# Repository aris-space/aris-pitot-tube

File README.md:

# ARIS Pitot Tube 

This pitot tube prototype is designed as an all-in-one plug-and-play system to gather data.  

The controller is based on an STM32F405 and mounted directly to the tube along with two MS5803 barometers, one MCP9600 thermocouple ADC, one ICM20601 accelerometer, an SD card and a battery.  
The software uses freeRTOS and will put the MCU in standby mode until the IMU wakes it up during lift-off (interrupt out of IMU to wakeup pin 1 on MCU).  
Preliminary measurements show that the current consumption in flight mode is 150mA and in sleep mode 3mA. With a 240mAh battery, this allows for 80h of sleep time or 1.6h of flight time.  

Below is a diagram explaining the software architecture.  

Repo structure:  
`Hardware` contains all step files and technical drawings to manufacture and assemble the structural components as well as the EAGLE files of the electronics hardware  
`Core/Inc` contains headers of project specific code  
`Core/Src` contains source of project specific code  
`Python` contains python code for analysis (including supersonic flight data from SPAC2022, HELVETIA)

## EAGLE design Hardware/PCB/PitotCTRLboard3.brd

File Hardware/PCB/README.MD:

`PitotCTRLboard2` is the old control board with micro USB and custom debug connector  

`PitotCTRLboard3` is the new control board with USB-C and Tag-Connect debug connector (PCB is slightly longer)  

`PitotPboard3` is the sensor board, where the barometers are mounted

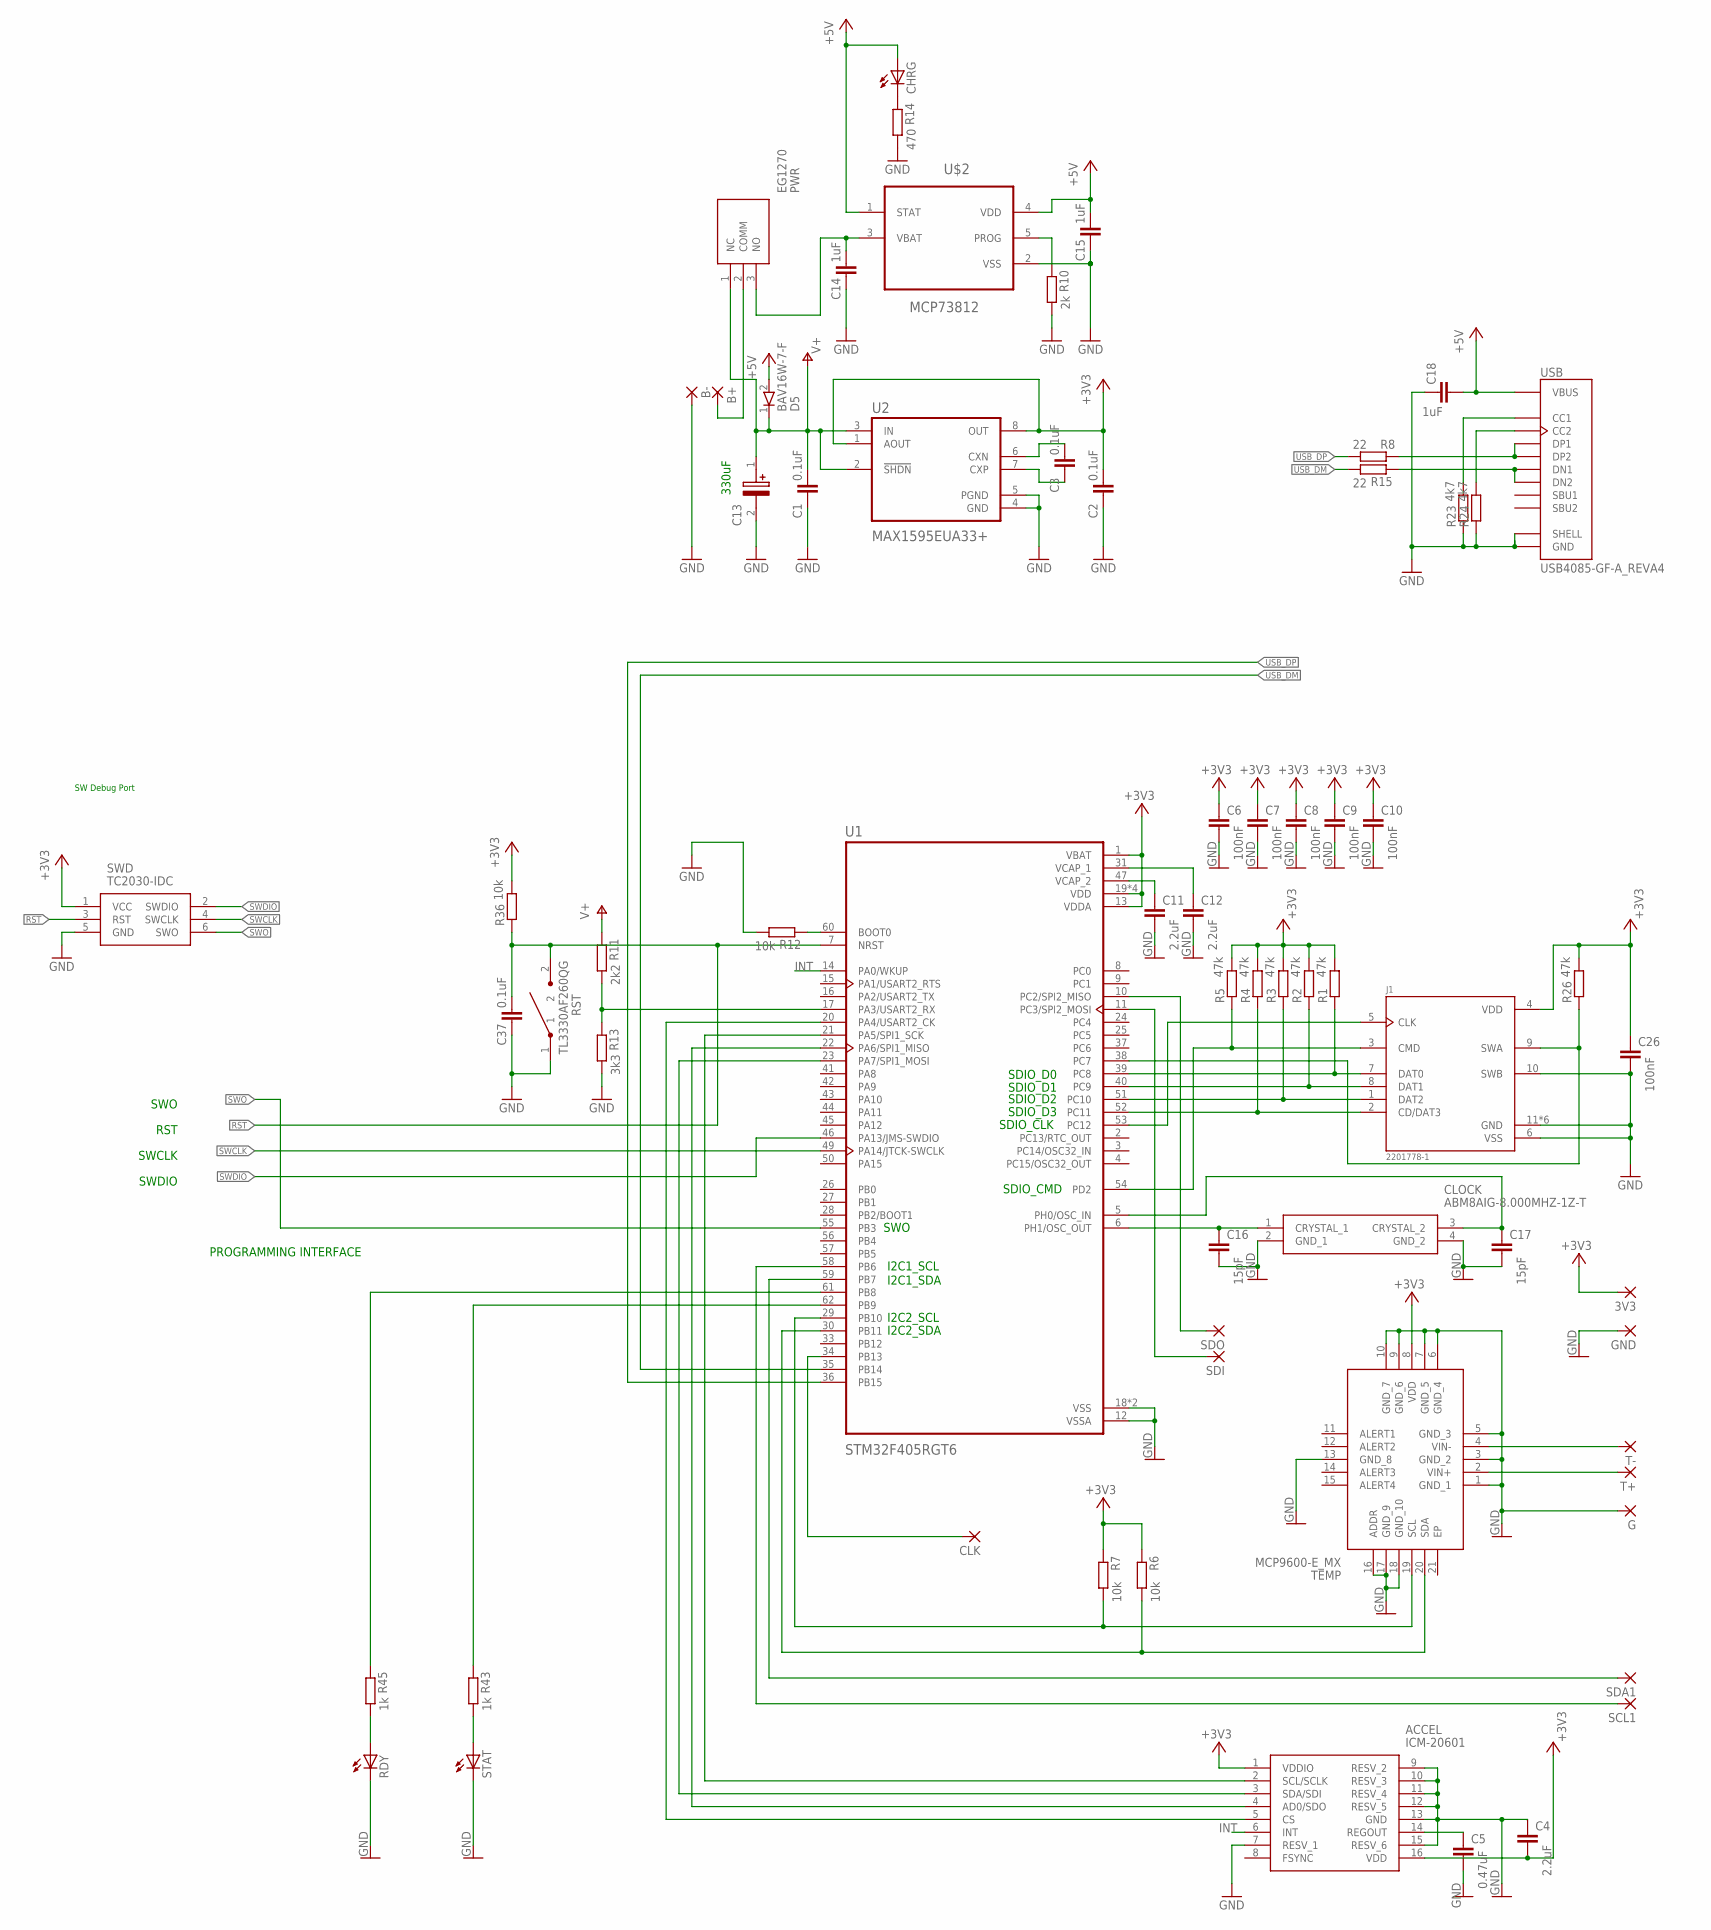
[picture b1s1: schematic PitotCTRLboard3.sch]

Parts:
3V3: SMD2; SMD1,27-2,54
ACCEL: ICM-20601; PULL-BACK-QFN-16
B+: 1,6/0,9
B-: 1,6/0,9
C1, C2, C3, C37: 0.1uF; C0603K
C4, C11, C12: 2.2uF; C0603K
C5: 0.47uF; C0603K
C6, C7, C8, C9, C10, C26: 100nF; C0603K
C13: 330uF; CAPPM6032X280N
C14, C15, C18: 1uF; C0603K
C16, C17: 15pF; C0603K
CHRG: LEDCHIPLED_0805; CHIPLED_0805
CLK: SMD2; SMD1,27-2,54
CLOCK: ABM8AIG-8.000MHZ-1Z-T; ABM8AIG8000MHZ1ZT
D5: BAV16W-7-F; SOD3716X145N
G: 1,6/0,9
GND: SMD2; SMD1,27-2,54
J1: 2201778-1; TE_2201778-1
PWR: EG1270
R1, R2, R3, R4, R5, R26: 47k; R0603
R6, R7, R12, R36: 10k; R0603
R8, R15: 22; R0603
R10: 2k; R0603
R11: 2k2; R0603
R13: 3k3; R0603
R14: 470; R0603
R23, R24: 4k7; R0603
R43, R45: 1k; R0603
RDY: LEDCHIPLED_0805; CHIPLED_0805
RST: TL3330AF260QG; TL3330
SCL1: SMD2; SMD1,27-2,54
SDA1: SMD2; SMD1,27-2,54
SDI: SMD2; SMD1,27-2,54
SDO: SMD2; SMD1,27-2,54
STAT: LEDCHIPLED_0805; CHIPLED_0805
SWD: TC2030-IDC; TC2030IDC
T+: 1,6/0,9
T-: 1,6/0,9
TEMP: MCP9600-E_MX; QFN65P500X500X100-21N
U1: STM32F405RGT6; QFP50P1200X1200X160-64N
U2: MAX1595EUA33+; SOP65P490X110-8N
U$2: MCP73812; SOT95P280X145-5N
USB: USB4085-GF-A_REVA4; GCT_USB4085-GF-A_REVA4

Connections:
+3V3: 3V3.1, ACCEL.1 (VDDIO), ACCEL.16 (VDD), C2.1, C4.2, C6.1, C7.1, C8.1, C9.1, C10.1, C26.1, J1.4 (VDD), R1.2, R2.2, R3.2, R4.2, R5.2, R6.1, R7.1, R26.2, R36.2, SWD.1 (VCC), TEMP.8 (VDD), U1.1 (VBAT), U1.13 (VDDA), U1.19 (VDD), U1.32 (VDD), U1.48 (VDD), U1.64 (VDD), U2.1 (AOUT), U2.8 (OUT)
+5V: C15.1, C18.2, CHRG.A, D5.2 (A), U$2.1 (STAT), U$2.4 (VDD), USB.A4 (VBUS), USB.A9 (VBUS), USB.B4 (VBUS), USB.B9 (VBUS)
GND: ACCEL.7 (RESV_1), ACCEL.9 (RESV_2), ACCEL.10 (RESV_3), ACCEL.11 (RESV_4), ACCEL.12 (RESV_5), ACCEL.13 (GND), ACCEL.15 (RESV_6), B-.1, C1.2, C2.2, C4.1, C5.2, C6.2, C7.2, C8.2, C9.2, C10.2, C11.2, C12.2, C13.2 (-), C14.2, C15.2, C16.2, C17.2, C18.1, C26.2, C37.2, CLOCK.2 (GND_1), CLOCK.4 (GND_2), G.1, GND.1, J1.6 (VSS), J1.10 (SWB), J1.11 (GND), J1.12 (GND), J1.13 (GND), J1.14 (GND), J1.15 (GND), J1.16 (GND), R10.2, R12.2, R13.2, R14.2, R23.1, R24.1, RDY.C, RST.1, STAT.C, SWD.5 (GND), TEMP.1 (GND_1), TEMP.3 (GND_2), TEMP.5 (GND_3), TEMP.6 (GND_4), TEMP.7 (GND_5), TEMP.9 (GND_6), TEMP.10 (GND_7), TEMP.13 (GND_8), TEMP.16 (ADDR), TEMP.17 (GND_9), TEMP.18 (GND_10), U1.12 (VSSA), U1.18 (VSS), U1.63 (VSS), U2.4 (GND), U2.5 (PGND), U$2.2 (VSS), USB.A1 (GND), USB.A12 (GND), USB.B1 (GND), USB.B12 (GND), USB.P1 (SHELL), USB.P2 (SHELL), USB.P3 (SHELL), USB.P4 (SHELL)
INT: ACCEL.6 (INT), U1.14 (PA0/WKUP)
unnamed: T-.1, TEMP.4 (VIN-)
unnamed: T+.1, TEMP.2 (VIN+)
unnamed: SDA1.1, U1.59 (PB7)
unnamed: SCL1.1, U1.58 (PB6)
unnamed: J1.7 (DAT0), R1.1, U1.39 (PC8)
unnamed: J1.8 (DAT1), R2.1, U1.40 (PC9)
unnamed: J1.1 (DAT2), R3.1, U1.51 (PC10)
unnamed: J1.2 (CD/DAT3), R4.1, U1.52 (PC11)
unnamed: J1.3 (CMD), R5.1, U1.54 (PD2)
unnamed: R7.2, TEMP.19 (SCL), U1.29 (PB10)
unnamed: R6.2, TEMP.20 (SDA), U1.30 (PB11)
unnamed: ACCEL.2 (SCL/SCLK), U1.21 (PA5/SPI1_SCK)
unnamed: ACCEL.4 (AD0/SDO), U1.22 (PA6/SPI1_MISO)
unnamed: ACCEL.3 (SDA/SDI), U1.23 (PA7/SPI1_MOSI)
unnamed: ACCEL.5 (CS), U1.20 (PA4/USART2_CK)
unnamed: J1.5 (CLK), U1.53 (PC12)
unnamed: R12.1, U1.60 (BOOT0)
unnamed: R43.2, STAT.A
unnamed: R43.1, U1.62 (PB9)
unnamed: R45.1, U1.61 (PB8)
unnamed: C17.1, CLOCK.3 (CRYSTAL_2), U1.5 (PH0/OSC_IN)
unnamed: B+.1, PWR.2 (COMM)
unnamed: C3.1, U2.6 (CXN)
unnamed: C3.2, U2.7 (CXP)
unnamed: ACCEL.14 (REGOUT), C5.1
unnamed: C12.1, U1.31 (VCAP_1)
unnamed: C11.1, U1.47 (VCAP_2)
unnamed: R10.1, U$2.5 (PROG)
unnamed: R11.2, R13.1, U1.17 (PA3/USART2_RX)
unnamed: C14.1, PWR.3 (NO), U$2.3 (VBAT)
unnamed: C16.1, CLOCK.1 (CRYSTAL_1), U1.6 (PH1/OSC_OUT)
unnamed: R8.1, USB.A6 (DP1), USB.B6 (DP2)
unnamed: CHRG.C, R14.1
unnamed: SDO.1, U1.10 (PC2/SPI2_MISO)
unnamed: SDI.1, U1.11 (PC3/SPI2_MOSI)
unnamed: CLK.1, U1.34 (PB13)
unnamed: R24.2, USB.B5 (CC2)
unnamed: R23.2, USB.A5 (CC1)
unnamed: R45.2, RDY.A
unnamed: R15.1, USB.A7 (DN1), USB.B7 (DN2)
unnamed: J1.9 (SWA), R26.1, U1.38 (PC7)
RST: C37.1, R36.1, RST.2, SWD.3 (RST), U1.7 (NRST)
SWCLK: SWD.4 (SWCLK), U1.49 (PA14/JTCK-SWCLK)
SWDIO: SWD.2 (SWDIO), U1.46 (PA13/JMS-SWDIO)
SWO: SWD.6 (SWO), U1.55 (PB3)
USB_DM: R15.2, U1.35 (PB14)
USB_DP: R8.2, U1.36 (PB15)
V+: C1.1, C13.1 (+), D5.1 (K), PWR.1 (NC), R11.1, U2.2 (!SHDN), U2.3 (IN)

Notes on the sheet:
RST
SWDIO
SWCLK
PROGRAMMING INTERFACE
SWO
I2C2_SCL
I2C2_SDA
I2C1_SCL
I2C1_SDA
SDIO_D2
SDIO_D3
SDIO_CLK
SDIO_D1
SDIO_D0
SDIO_CMD
330uF
SW Debug Port

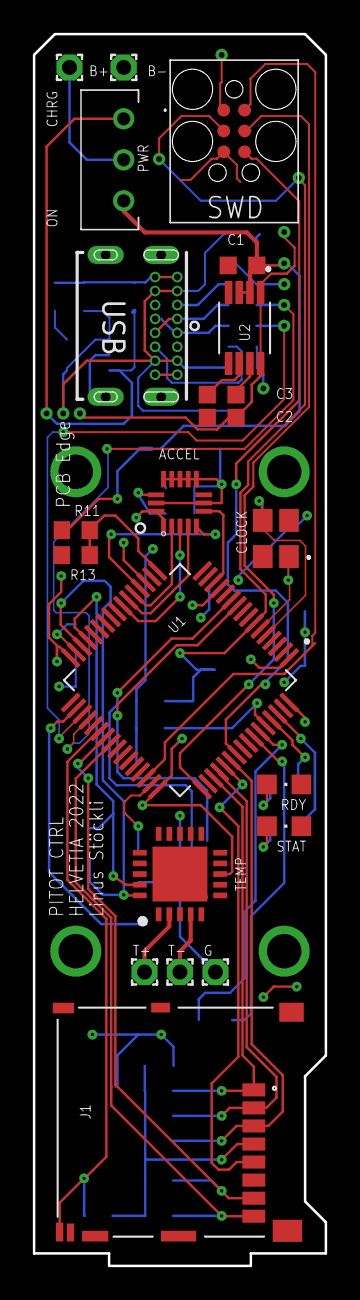
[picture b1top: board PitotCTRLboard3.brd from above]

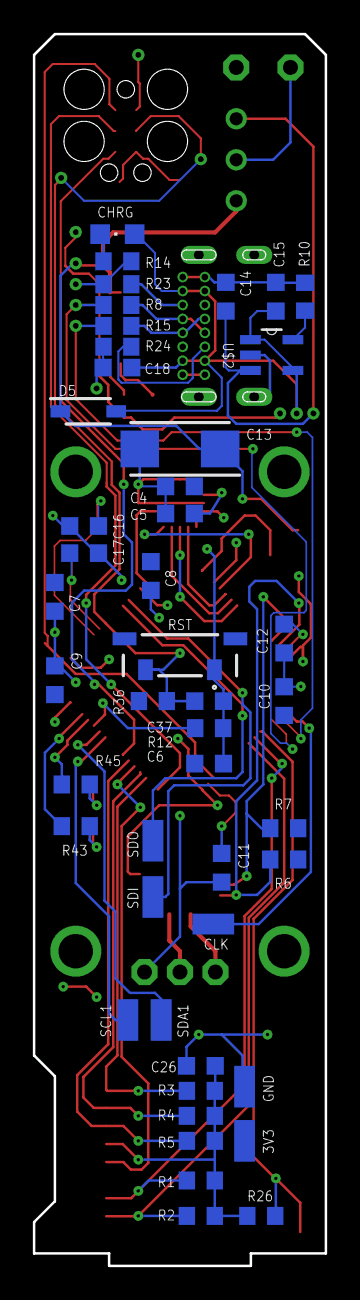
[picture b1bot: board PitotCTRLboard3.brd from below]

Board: 2 copper layers, 17.8 x 75.1 mm, 67 parts (46 on the bottom side), 52 nets.

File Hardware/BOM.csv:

Qty;Value;Device;Package;Parts;Description;ALLIED_NUMBER;ALLIED_PRICE-STOCK;ARROW_PART_NUMBER;ARROW_PRICE-STOCK;AVAILABILITY;CUI_PURCHASE_URL;DESCRIPTION;DIGIKEY-PURCHASE-URL;HEIGHT;MANUFACTURER;MANUFACTURER_NAME;MANUFACTURER_PART_NUMBER;MF;MOUSER-PURCHASE-URL;MOUSER_PART_NUMBER;MOUSER_PRICE-STOCK;MP;PACKAGE;PARTREV;PRICE;RS_PART_NUMBER;RS_PRICE-STOCK;SPICEPREFIX;STANDARD
3;;LEDCHIPLED_0805;CHIPLED_0805;CHRG, RDY, STAT;LED;;;;;;;;;;;;;;;;;;;;;;;;
12;0.1uF;C-EUC0603K;C0603K;C1, C2, C3, C37;CAPACITOR, European symbol;;;;;;;;;;;;;;;;;;;;;;;C;
1;0.47uF;C-EUC0603K;C0603K;C5;CAPACITOR, European symbol;;;;;;;;;;;;;;;;;;;;;;;C;
6;10k;R-EU_R0603;R0603;R6, R7, R8, R9, R12, R36;RESISTOR, European symbol;;;;;;;;;;;;;;;;;;;;;;;R;
2;15pF;C-EUC0603K;C0603K;C16, C17;CAPACITOR, European symbol;;;;;;;;;;;;;;;;;;;;;;;C;
2;1k;R-EU_R0603;R0603;R43, R45;RESISTOR, European symbol;;;;;;;;;;;;;;;;;;;;;;;R;
2;1uF;C-EUC0603K;C0603K;C14, C15;CAPACITOR, European symbol;;;;;;;;;;;;;;;;;;;;;;;C;
3;2.2uF;C-EUC0603K;C0603K;C4, C11, C12;CAPACITOR, European symbol;;;;;;;;;;;;;;;;;;;;;;;C;
1;2201778-1;2201778-1;TE_2201778-1;J1;MICRO SD PUSH PUSH LOW PROFILE TYPE;;;;;;;;;;TE Connectivity;;;;;;;;;B;;;;;Manufacturer recommendations
1;2k;R-EU_R0603;R0603;R10;RESISTOR, European symbol;;;;;;;;;;;;;;;;;;;;;;;R;
1;2k2;R-EU_R0603;R0603;R11;RESISTOR, European symbol;;;;;;;;;;;;;;;;;;;;;;;R;
1;330uF;T491C106K035AT;CAPPM6032X280N;C13;KEMET 10uF 35V dc Tantalum Capacitor MnO2 Solid +/-10% Tolerance T491 Series;70610893;https://www.alliedelec.com/kemet-t491c106k035at/70610893/;;;;;KEMET 10uF 35V dc Tantalum Capacitor MnO2 Solid +/-10% Tolerance T491 Series;;2.8mm;;Kemet;T491C106K035AT;;;80-T491C106K035;https://www.mouser.com/Search/Refine.aspx?Keyword=80-T491C106K035;;;;;8015520;https://uk.rs-online.com/web/p/products/8015520;;
1;3k3;R-EU_R0603;R0603;R13;RESISTOR, European symbol;;;;;;;;;;;;;;;;;;;;;;;R;
1;470;R-EU_R0603;R0603;R14;RESISTOR, European symbol;;;;;;;;;;;;;;;;;;;;;;;R;
6;47k;R-EU_R0603;R0603;R1, R2, R3, R4, R5, R26;RESISTOR, European symbol;;;;;;;;;;;;;;;;;;;;;;;R;
1;ABM8AIG-8.000MHZ-1Z-T;ABM8AIG-8.000MHZ-1Z-T;ABM8AIG8000MHZ1ZT;CLOCK;Crystals 18pF 8MHz 10ppm AEC-Q200 -40C +125C;;;;;;;Crystals 18pF 8MHz 10ppm AEC-Q200 -40C +125C;;0.8mm;;ABRACON;ABM8AIG-8.000MHZ-1Z-T;;;815-M8AIG-8-1ZT;https://www.mouser.com/Search/Refine.aspx?Keyword=815-M8AIG-8-1ZT;;;;;;;;
1;BAV16W-7-F;BAV16W-7-F;SOD3716X145N;D5;Diode Switching 100V 0.15A 2Pin SOD123 Diodes Inc BAV16W-7-F Switching Diode, 300mA 100V, 2-Pin SOD-123;70437641;http://www.alliedelec.com/diodes-inc-bav16w-7-f/70437641/;;;;;Diode Switching 100V 0.15A 2Pin SOD123 Diodes Inc BAV16W-7-F Switching Diode, 300mA 100V, 2-Pin SOD-123;;1.45mm;;Diodes Inc.;BAV16W-7-F;;;621-BAV16W-F;https://www.mouser.com/Search/Refine.aspx?Keyword=621-BAV16W-F;;;;;7513430P;http://uk.rs-online.com/web/p/products/7513430P;;
1;DEBUG;DEBUG CONNECTOR;DEBUG;U$1;https://www.mouser.ch/ProductDetail/474-PRT-10361;;;;;;;;;;;;;;;;;;;;;;;;
1;EG1270;EG1270;EG1270;PWR;E-SWITCH - EG1270 - SWITCH, SLIDE, SPDT, 300mA, 6V, PCB;;;EG1270;;;;E-SWITCH - EG1270 - SWITCH, SLIDE, SPDT, 300mA, 6V, PCB;;4.6mm;;E-Switch;EG1270;;;612-EG1270;https://www.mouser.co.uk/ProductDetail/E-Switch/EG1270?qs=xD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;;;;;;;;
1;ICM-20601;ICM-20601;PULL-BACK-QFN-16;ACCEL;IMU ACCEL/GYRO/TEMP I2C/SPI LGA;;;;;;;IMU ACCEL/GYRO/TEMP I2C/SPI LGA;;mm;;InvenSense Inc.;ICM-20601;;;410-ICM-20601;https://www.mouser.com/Search/Refine.aspx?Keyword=410-ICM-20601;;;;;;;;
1;MAX1595EUA33+;MAX1595EUA33+;SOP65P490X110-8N;U2;None;;;;;Unavailable;; Charge Pump Switching Regulator IC Positive Fixed 3.3V 1 Output 125mA 8-TSSOP, 8-MSOP (0.118, 3.00mm Width) ;;;;;;Maxim Integrated;;;;MAX1595EUA33;None;;None;;;;
1;MCP73812;MCP73831T-2ACI/OT;SOT95P280X145-5N;U$2;Charge Management Controller Buy Part;;;;;Warning;; Charger IC Lithium Ion/Polymer SOT-23-5 ;https://snapeda.com/shop?store=DigiKey&id=53208;;;;;Microchip;https://snapeda.com/shop?store=Mouser&id=53208;;;MCP73831T-2ACI/OT;SOT-23 Microchip;;None;;;;
1;MCP9600-E_MX;MCP9600-E_MX;QFN65P500X500X100-21N;TEMP;Board Mount Temperature Sensors Thermocouple to I2C converter;;;;;;;Board Mount Temperature Sensors Thermocouple to I2C converter;;1mm;;Microchip;MCP9600-E/MX;;;579-MCP9600-E/MX;https://www.mouser.com/Search/Refine.aspx?Keyword=579-MCP960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;;;;;1717832P;http://uk.rs-online.com/web/p/products/1717832P;;
1;STM32F405RGT6;STM32F405RGT6;QFP50P1200X1200X160-64N;U1;High-performance foundation line, ARM Cortex-M4 core with DSP and FPU, 1 Mbyte Flash, 168 MHz CPU, ART Accelerator;;;;;Unavailable;; ARM® Cortex®-M4 STM32F4 Microcontroller IC 32-Bit 168MHz 1MB (1M x 8) FLASH 64-LQFP (10x10) ;;;;;;STMicroelectronics;;;;STM32F405RGT6;LQFP-64 STMicroelectronics;;None;;;;
1;TL3330AF260QG;TL3330AF260QG;TL3330;RST;Tactile Switches 50mA@12VDC 260g OF Silver contacts;;;;;;;Tactile Switches 50mA@12VDC 260g OF Silver contacts;;mm;;E-Switch;TL3330AF260QG;;;612-TL3330AF260QG;https://www.mouser.co.uk/ProductDetail/E-Switch/TL3330AF260Q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;;;;;;;;
1;UJ2-MIBH2-4-SMT-TR;UJ2-MIBH2-4-SMT-TR;CUI_UJ2-MIBH2-4-SMT-TR;USB;Micro B Type 5 Pin Horizontal 30 µin Plating SMT USB Jack 2.0 Buy Part;;;;;Warning;https://www.cuidevices.com/product/interconnect/connectors/u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;Micro B, USB 2.0, 1.8 A, Right Angle, Surface Mount (SMT), USB Receptacle;https://snapeda.com/shop?store=DigiKey&id=702231;;;;;CUI Devices;https://snapeda.com/shop?store=Mouser&id=702231;;;UJ2-MIBH2-4-SMT-TR;None;;None;;;;
2;MS580314BA01-00;MS580314BA01-00;MS580314BA0100;IC1, IC2;Sensor Pressure SMD MS5803-14BA 14bar;MS580314BA01-00;https://www.arrow.com/en/products/ms580314ba01-00/te-connectivity;Sensor Pressure SMD MS5803-14BA 14bar;3.03mm;TE Connectivity;MS580314BA01-00;824-MS580314BA01-00;https://www.mouser.co.uk/ProductDetail/Measurement-Specialti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;;;;;;;;;;;;;;;;
1;K-Type;Thermocouple;;;at least 30cm of insulated wires;;;;;;;;;;;;;;;;;;;;;;;;

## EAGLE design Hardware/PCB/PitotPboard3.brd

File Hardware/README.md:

The CAD with step files and technical drawings can be found in the `CAD` folder.  
`PCB/PitotCTRLBoard` is the controller PCB with the MCU, IMU, ADC and SD-card on it  
`PCB/PitotPBoard3` is the sensor board containing the two Barometers  
The two boards are connected with 3V3, GND, and two I2C lines.  
Consult the `BOM.csv` to order the components, and `assembly_instructions.txt` to mount the hardware.  
`TODO.txt` contains a list of possible improvoments for future interations

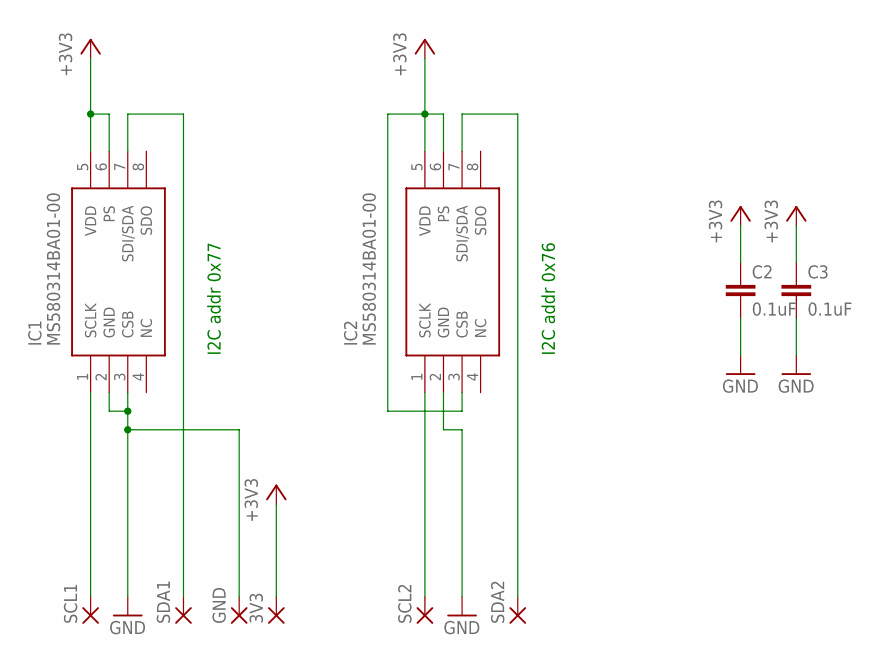
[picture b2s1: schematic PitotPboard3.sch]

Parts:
3V3: 1,6/0,9
C2, C3: 0.1uF; C0603K
GND: 1,6/0,9
IC1, IC2: MS580314BA01-00; MS580314BA0100
SCL1, SCL2: 1,6/0,9
SDA1, SDA2: 1,6/0,9

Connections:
+3V3: 3V3.1, C2.1, C3.1, IC1.5 (VDD), IC1.6 (PS), IC2.3 (CSB), IC2.5 (VDD), IC2.6 (PS)
GND: C2.2, C3.2, GND.1, IC1.2 (GND), IC1.3 (CSB), IC2.2 (GND)
unnamed: IC2.1 (SCLK), SCL2.1
unnamed: IC2.7 (SDI/SDA), SDA2.1
unnamed: IC1.7 (SDI/SDA), SDA1.1
SCK: IC1.1 (SCLK), SCL1.1

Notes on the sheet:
I2C addr 0x77
I2C addr 0x76

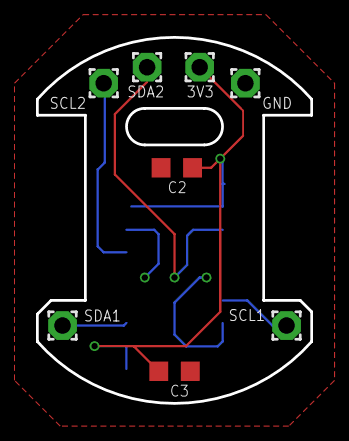
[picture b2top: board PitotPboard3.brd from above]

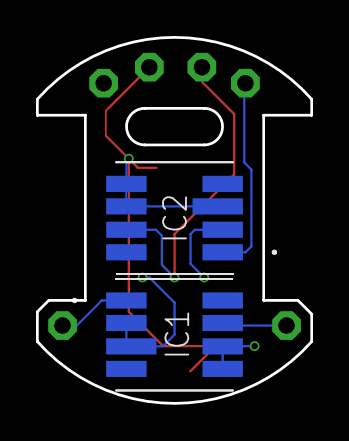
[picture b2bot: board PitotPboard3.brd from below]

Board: 2 copper layers, 15.2 x 20.3 mm, 10 parts (2 on the bottom side), 6 nets.

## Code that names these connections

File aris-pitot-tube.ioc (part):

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Mcu.Name=STM32F405RGTx
Mcu.Package=LQFP64
Mcu.UserName=STM32F405RGTx
PA0-WKUP.Mode=SYS_WakeUp0
PA0-WKUP.Signal=SYS_WKUP
PA13.Mode=Trace_Asynchronous_SW
PA13.Signal=SYS_JTMS-SWDIO
PA14.Mode=Trace_Asynchronous_SW
PA14.Signal=SYS_JTCK-SWCLK
PA4.GPIOParameters=GPIO_Label
PA4.GPIO_Label=SPI1_CS
PA4.Signal=GPIO_Output
PA5.Mode=Full_Duplex_Master
PA5.Signal=SPI1_SCK
PA6.Mode=Full_Duplex_Master
PA6.Signal=SPI1_MISO
PA7.Mode=Full_Duplex_Master
PA7.Signal=SPI1_MOSI
PB10.GPIOParameters=GPIO_Pu
PB10.GPIO_Pu=GPIO_PULLUP
PB10.Mode=I2C
PB10.Signal=I2C2_SCL
PB11.GPIOParameters=GPIO_Pu
PB11.GPIO_Pu=GPIO_PULLUP
PB11.Mode=I2C
PB11.Signal=I2C2_SDA
PB3.Mode=Trace_Asynchronous_SW
PB3.Signal=SYS_JTDO-SWO
PB6.GPIOParameters=GPIO_Pu
PB6.GPIO_Pu=GPIO_PULLUP
PB6.Mode=I2C
PB6.Signal=I2C1_SCL
PB7.GPIOParameters=GPIO_Pu
PB7.GPIO_Pu=GPIO_PULLUP
PB7.Mode=I2C
PB7.Signal=I2C1_SDA
PB8.GPIOParameters=GPIO_Label
PB8.GPIO_Label=RDY
PB8.Signal=GPIO_Output
PB9.GPIOParameters=GPIO_Label
PB9.GPIO_Label=STAT
PB9.Signal=GPIO_Output
PC10.GPIOParameters=GPIO_PuPd
PC10.GPIO_PuPd=GPIO_PULLUP
PC10.Mode=SD_4_bits_Wide_bus
PC10.Signal=SDIO_D2
PC11.GPIOParameters=GPIO_PuPd
PC11.GPIO_PuPd=GPIO_PULLUP
PC11.Mode=SD_4_bits_Wide_bus
PC11.Signal=SDIO_D3
PC12.GPIOParameters=GPIO_PuPd
PC12.GPIO_PuPd=GPIO_NOPULL
PC12.Mode=SD_4_bits_Wide_bus
PC12.Signal=SDIO_CK
PC7.Signal=GPIO_Input
PC8.GPIOParameters=GPIO_PuPd
PC8.GPIO_PuPd=GPIO_PULLUP
PC8.Mode=SD_4_bits_Wide_bus
PC8.Signal=SDIO_D0
PC9.GPIOParameters=GPIO_PuPd
PC9.GPIO_PuPd=GPIO_PULLUP
PC9.Mode=SD_4_bits_Wide_bus
PC9.Signal=SDIO_D1
PD2.GPIOParameters=GPIO_PuPd
PD2.GPIO_PuPd=GPIO_PULLUP
PD2.Mode=SD_4_bits_Wide_bus
PD2.Signal=SDIO_CMD
PH0-OSC_IN.Mode=HSE-External-Oscillator
PH0-OSC_IN.Signal=RCC_OSC_IN
PH1-OSC_OUT.Mode=HSE-External-Oscillator
PH1-OSC_OUT.Signal=RCC_OSC_OUT
RCC.HSE_VALUE=8000000
RCC.SYSCLKFreq_VALUE=168000000
RCC.SYSCLKSource=RCC_SYSCLKSOURCE_PLLCLK
board=custom

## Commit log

2022-02-07 initial commit ( w/ code)
    tested stop mode and WOM interrupt
2022-02-08 Create LICENSE
2022-02-08 added author
2022-02-08 rename
2022-02-10 changed stop mode to standby mode and implemented binary saving to SD
2022-02-10 clean up idle detect function
2022-02-10 remove unused import
2022-02-10 clean up and implement length in idle detection
2022-02-10 add gitignore
2022-02-10 add project files for STM32CubeIDE
2022-02-10 add user-specific files to gitignore
2022-02-10 reformat
2022-02-17 check if sensor response is okay
2022-02-17 sensor response and new SD directories/file format
2022-02-17 change freeRTOS heap and SDIO clock
2022-02-21 added hardware files + software structure graph
2022-02-21 add png
2022-02-21 implemented gyro in idle detect
2022-02-22 add TODO and debug prints
2022-02-22 include gyro in idle detect
2022-02-22 add render of pitot tube
2022-02-22 rename log to cal
2022-02-24 add mutex and semaphores
2022-02-24 reformat code
2022-02-24 cubemx reformats everything back.. geil...
2022-02-24 add logging mutex
2022-03-02 change task priorities
2022-03-02 change SD buffering and minor updates
2022-03-02 typo fix
2022-03-03 Revert "add registers as defines"
    This reverts commit 5bf509e9cd9b998f265b85ade3e24de55e518b3e.
2022-03-03 add registers as defines
2022-03-03 add wait time dependent on osr
2022-03-03 add wait time
2022-03-03 fix baro
2022-03-03 add SD queue (slow...)
2022-03-03 implement DMA (I2C and SPI)
2022-03-03 add timer and configure trace to analyze freeRTOS CPU usage
2022-03-10 added schematics, pcb routing, TODO, BOM and assembly instructions
2022-03-10 added CAD
2022-03-10 change delimiter
2022-04-15 add battery to BOM.csv
2022-04-19 PCB fix
2022-04-21 add sensor-board gerber files
2022-04-21 add ctrl-board gerber files
2022-04-21 changed text from euler to helvetia
2022-04-22 added pitot ctrl board 3 (includes USBC and new debug connector)
2022-04-22 fix a via under usb-c
2022-04-22 fix via
2022-04-24 add latest render
2022-04-24 fix usb-c position
2022-04-25 change for latest jlc config
2022-05-20 bug fix
2022-09-19 add python files for analysis 📉
2022-09-19 add plot of HELVETIA@SPAC2022 🇨🇭
